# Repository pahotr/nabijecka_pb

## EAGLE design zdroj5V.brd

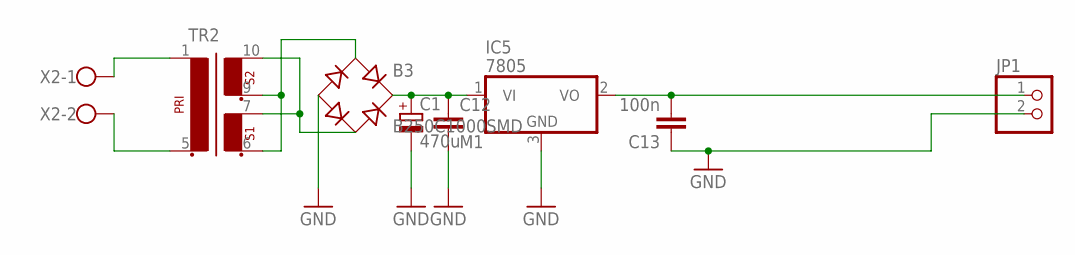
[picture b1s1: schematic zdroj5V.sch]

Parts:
B3: B250C1000SMD; B40S
C1: 470u; E5-10,5
C12: M1; C1206
C13: 100n; C1206
IC5: 7805; TO252
JP1: PINHD-1X2; 1X02
TR2: EI30-2
X2: W237-102

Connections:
GND: B3.-, C1.-, C12.2, C13.1, IC5.3 (GND), JP1.2
unnamed: B3.AC1, TR2.6 (3), TR2.9 (5)
unnamed: B3.+, C1.+, C12.1, IC5.1 (VI)
unnamed: B3.AC2, TR2.7 (4), TR2.10 (6)
unnamed: TR2.5 (2), X2.2
unnamed: TR2.1, X2.1
unnamed: C13.2, IC5.2 (VO), JP1.1

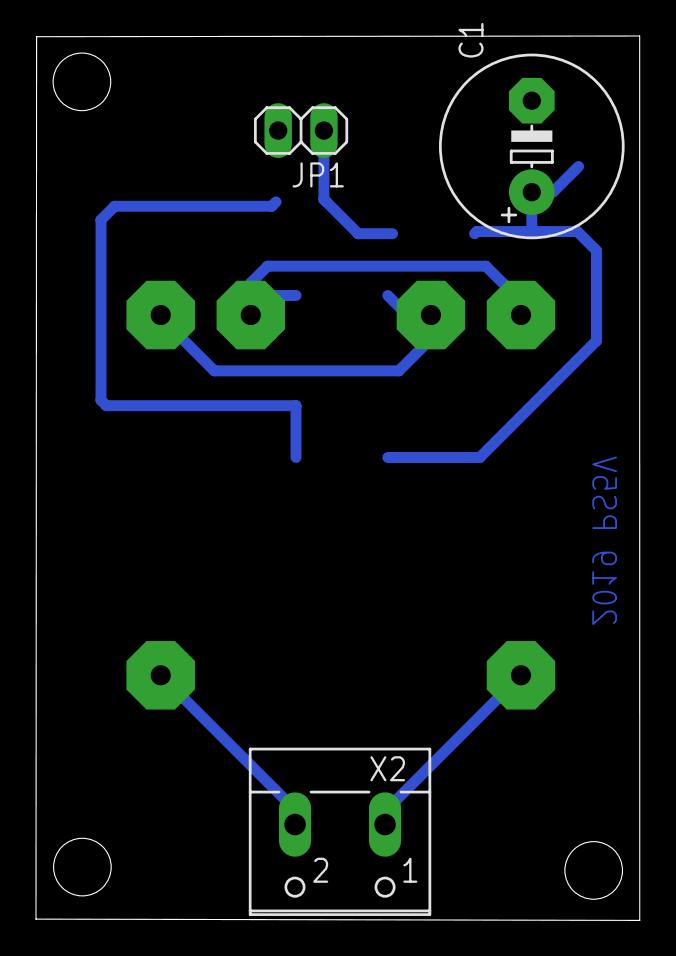
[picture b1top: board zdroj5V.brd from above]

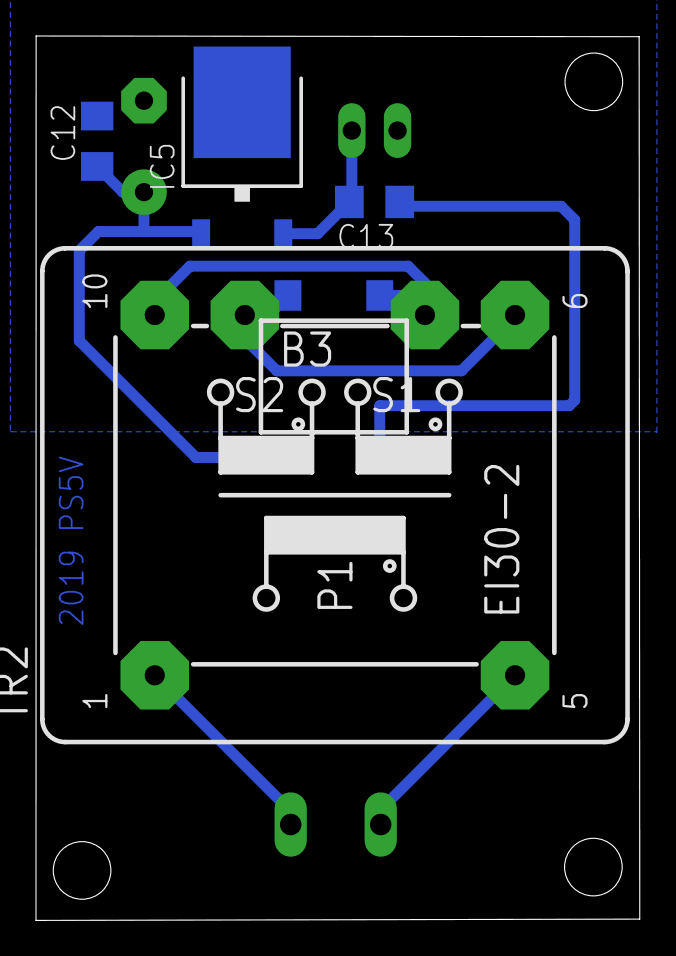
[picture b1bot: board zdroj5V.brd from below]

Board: 2 copper layers, 33.5 x 49.1 mm, 8 parts (5 on the bottom side), 7 nets.

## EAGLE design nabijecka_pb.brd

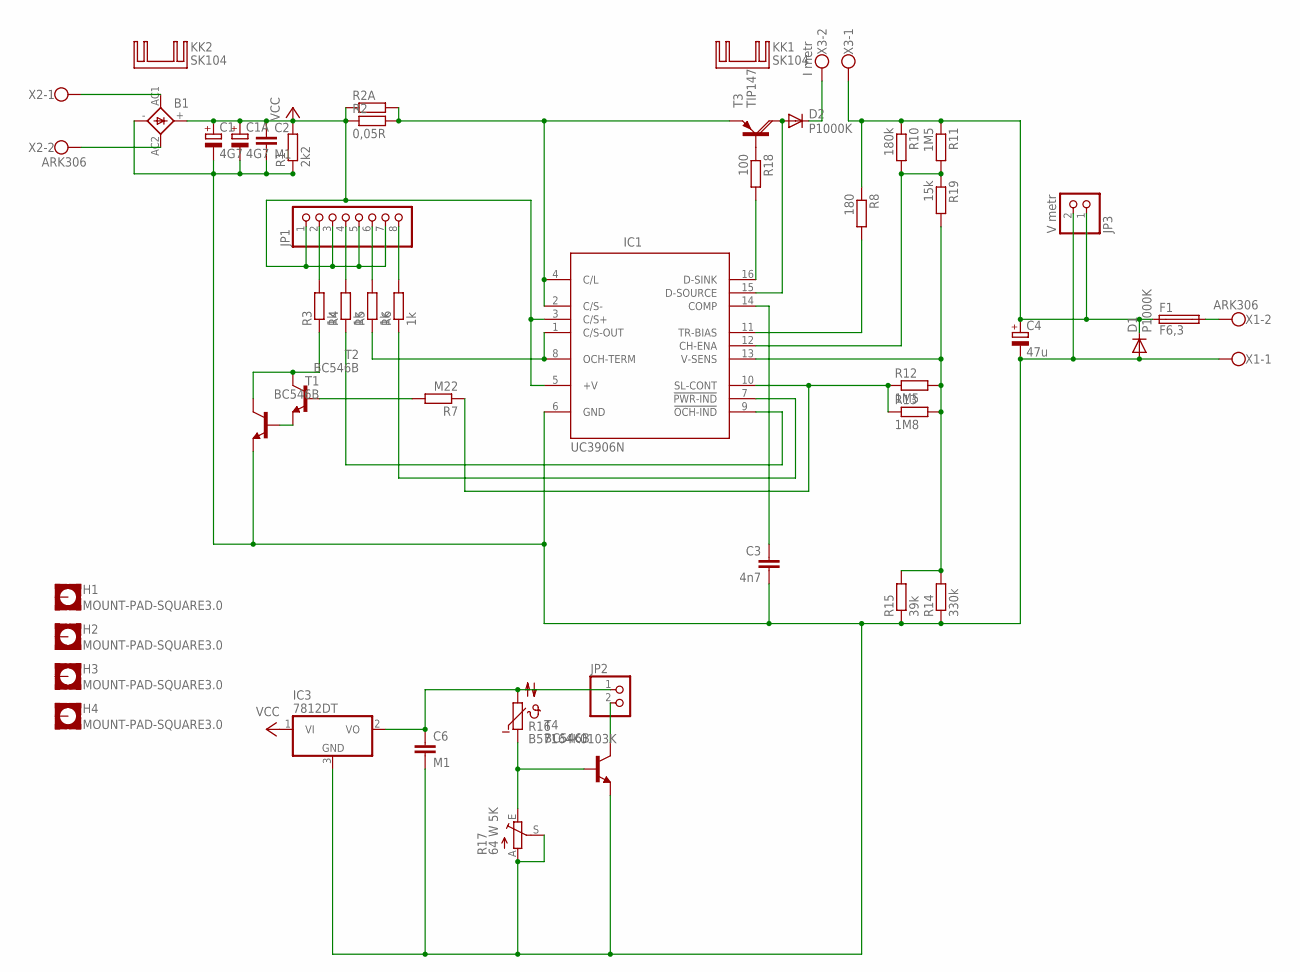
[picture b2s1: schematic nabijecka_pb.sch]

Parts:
B1: FB32
C1, C1A: 4G7; E7,5-18
C2: M1; C050-045X075
C3: 4n7; C050-045X075
C4: 47u; E2,5-6
C6: M1; C1206
D1, D2: P1000K; P6-15
F1: F6,3; F456
H1, H2, H3, H4: MOUNT-PAD-SQUARE3.0; 3,0-PAD-SQUARE
IC1: UC3906N; DIL16
IC3: 7812DT; TO252
JP1: PINHD-1X8; 1X08
JP2: PINHD-1X2; 1X02
JP3: V metr; 1X02
KK1, KK2: SK104
R1: 2k2; 0207/10
R2: 0,05R; P0817/22
R2A: R-EU_0817_22; P0817/22
R3, R4, R5, R6: 1k; 0207/10
R7: M22; 0207/10
R8: 180; 0207/10
R10: 180k; 0207/10
R11, R12: 1M5; 0207/10
R13: 1M8; 0207/10
R14: 330k; 0207/10
R15: 39k; 0207/10
R16: B57164K0103K; P642
R17: 64 W 5K; S64W
R18: 100; 0207/10
R19: 15k; 0207/10
T1, T2, T4: BC546B; TO92-EBC
T3: TIP147; SOT93
X1, X2: ARK306; W237-102
X3: I metr; W237-102

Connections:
unnamed: B1.AC1, X2.1
unnamed: B1.AC2, X2.2
unnamed: F1.2, X1.2
unnamed: IC1.2 (C/S-), IC1.4 (C/L), R2.2, R2A.2, T3.E
unnamed: JP1.4, R4.2
unnamed: JP1.2, R3.2
unnamed: D2.A, IC1.15 (D-SOURCE), T3.C
unnamed: JP1.6, R5.2
unnamed: JP1.8, R6.2
unnamed: R3.1, T1.C, T2.C
unnamed: R7.2, T2.B
unnamed: IC1.7 (!PWR-IND), R6.1
unnamed: IC1.1 (C/S-OUT), IC1.8 (OCH-TERM), R5.1
unnamed: IC1.9 (!OCH-IND), R4.1
unnamed: T1.B, T2.E
unnamed: IC1.10 (SL-CONT), R7.1, R12.1, R13.1
unnamed: R18.1, T3.B
unnamed: C4.+, D1.C, F1.1, JP3.1, R8.1, R10.1, R11.1, X3.1
unnamed: D2.C, X3.2
unnamed: C3.1, IC1.14 (COMP)
unnamed: IC1.11 (TR-BIAS), R8.2
unnamed: IC1.12 (CH-ENA), R10.2, R11.2, R19.1
unnamed: IC1.13 (V-SENS), R12.2, R13.2, R14.2, R15.2, R19.2
unnamed: R16.1, R17.E, T4.B
unnamed: C6.1, IC3.2 (VO), JP2.1, R16.2
unnamed: B1.-, C1.-, C1A.-, C2.2, C3.2, C4.-, C6.2, D1.A, IC1.6 (GND), IC3.3 (GND), JP3.2, R1.1, R14.1, R15.1, R17.A, R17.S, T1.E, T4.E, X1.1
unnamed: IC1.16 (D-SINK), R18.2
unnamed: JP2.2, T4.C
VCC: B1.+, C1.+, C1A.+, C2.1, IC1.3 (C/S+), IC1.5 (+V), IC3.1 (VI), JP1.1, JP1.3, JP1.5, JP1.7, R1.2, R2.1, R2A.1

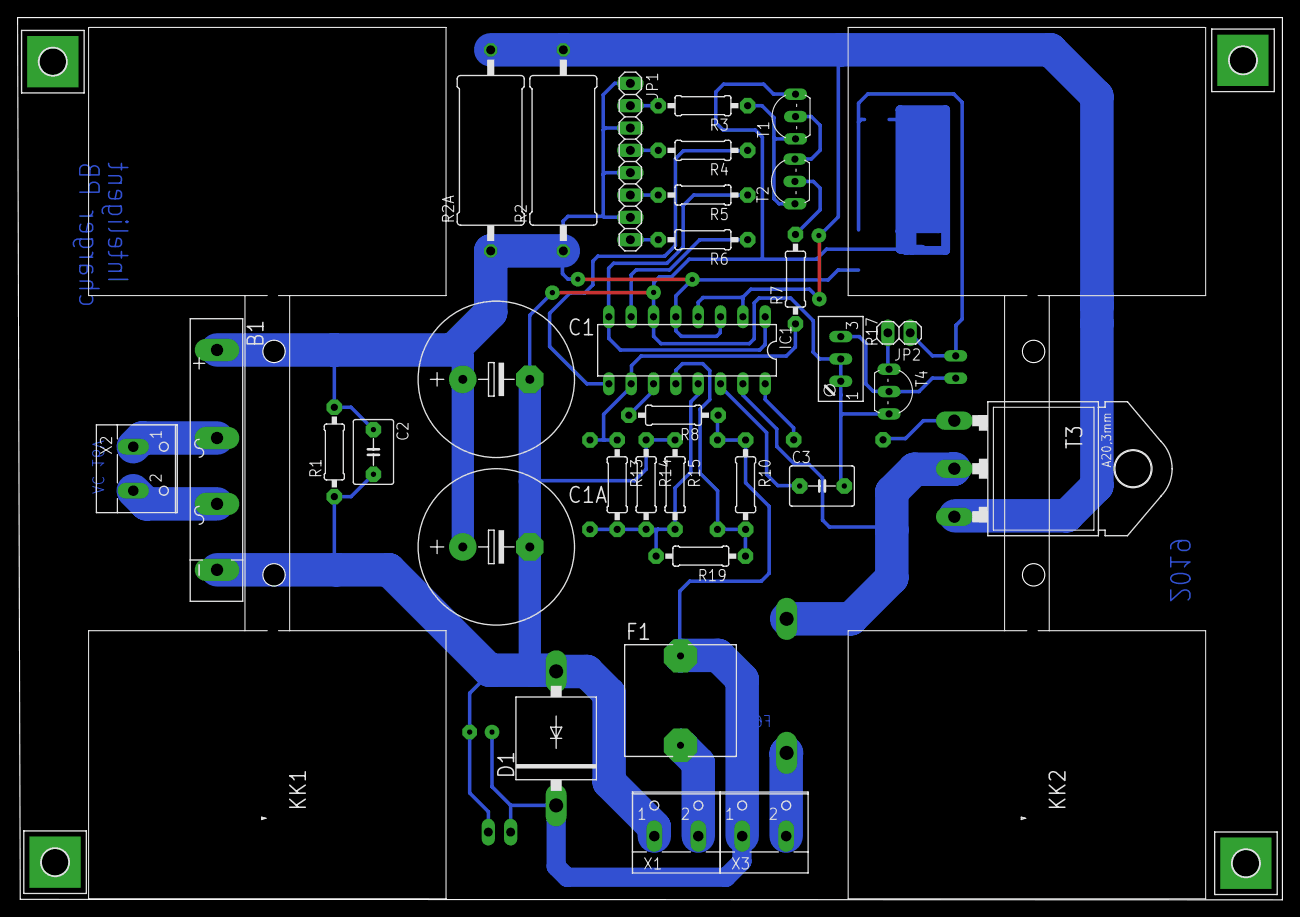
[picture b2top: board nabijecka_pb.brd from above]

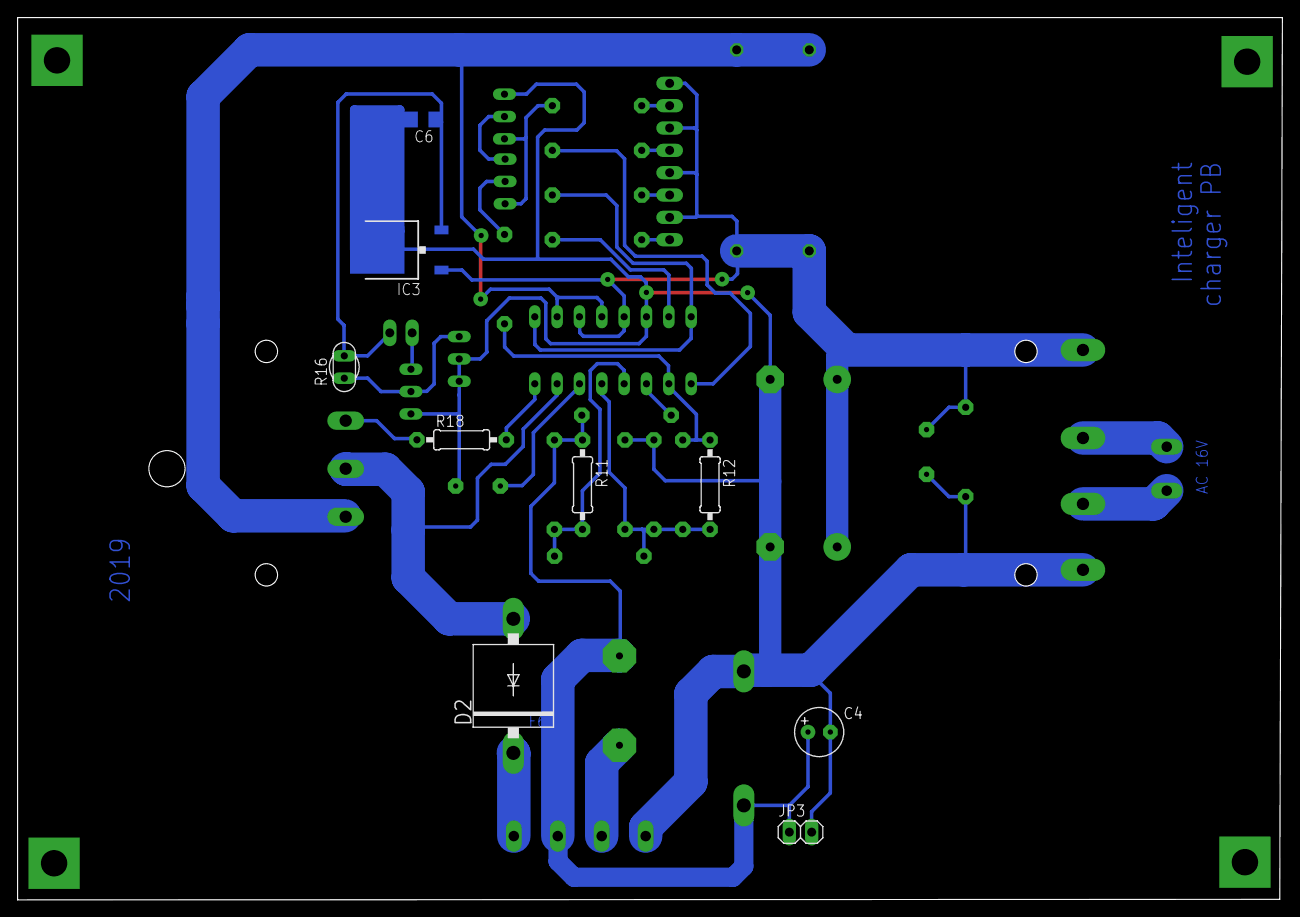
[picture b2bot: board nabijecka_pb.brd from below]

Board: 2 copper layers, 143.8 x 100.3 mm, 47 parts (9 on the bottom side), 29 nets.
